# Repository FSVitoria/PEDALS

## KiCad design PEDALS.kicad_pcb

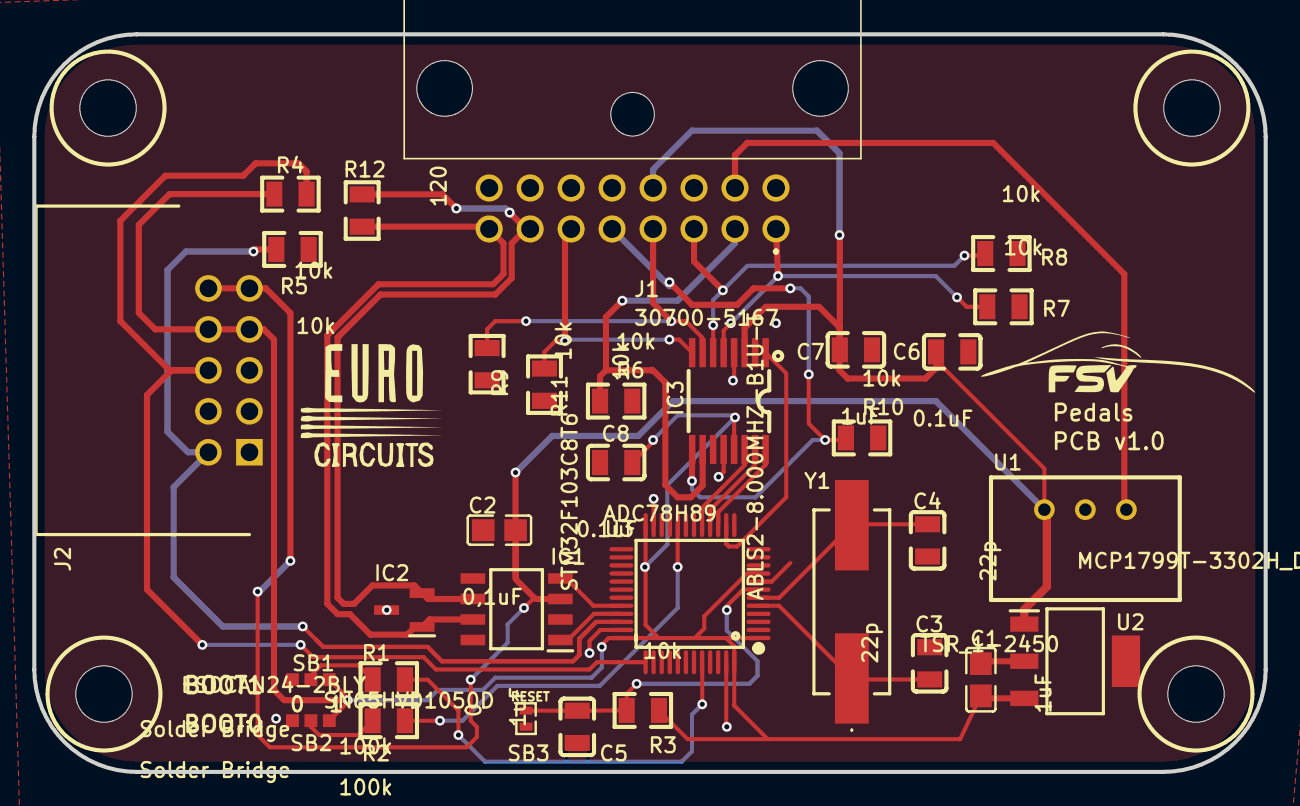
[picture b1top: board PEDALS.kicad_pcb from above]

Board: 2 copper layers, 76.3 x 45.7 mm, 36 parts (0 on the bottom side), 27 nets.

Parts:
C1, C5, C7: 1uF; C0805
C2: 0,1uF; C0805
C3, C4: 22p; C0805
C6, C8: 0.1uF; C0805
Hole_gge27180: Hole_gge27180
Hole_gge27183: Hole_gge27183
Hole_gge27186: Hole_gge27186
Hole_gge27189: Hole_gge27189
IC1: SN65HVD1050D; SOIC127P600X175-8N
IC2: ESDCAN24-2BLY; SOT105P255X150-3N
IC3: ADC78H89; TSSOP-16_L5.0-W4.4-P0.65-LS6.4-BL
J1: 30700-5167; 307005167
J2: 61201021721; SHDRRA10W64P254X254_2X5_2036X8
R1, R2: 100k; R0805
R3, R4, R5, R6, R7, R8, R9, R10, R11: 10k; R0805
R12: 120; R0805
SB1, SB2: Solder Bridge; SOLDER BRDIGE
SB3: 0; R0402
U1: TSR_1-2450; TSR-1-24120
U2: MCP1799T-3302H_DB; SOT230P700X180-4N
U3: STM32F103C8T6; LQFP-48_L7.0-W7.0-P0.50-LS9.0-BL
Y1: ABLS2-8.000MHZ-B1U-T; ABLS

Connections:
3V3: C1.2, C8.1, IC3.13, J2.7, J2.8, R3.2, R4.2, SB1.1, SB2.1, U2.3, U3.1, U3.9, U3.24, U3.36, U3.48
+5V: C2.1, C6.2, C7.2, IC1.3, IC3.3, J1.12, J2.9, J2.10, U1.3, U2.1
+24V: J1.10, U1.1
BOOT0: R1.1, U3.44
BOOT1: R2.1, U3.20
CAN_H: IC1.7, IC2.1, J1.8, R12.2
CAN_L: IC1.6, IC2.2, J1.7, R12.1
CAN_RX: IC1.4, U3.32
CAN_TX: IC1.1, U3.33
GND: C1.1, C2.2, C3.2, C4.2, C5.1, C6.1, C7.1, C8.2, IC1.2, IC1.8, IC2.3, IC3.4, IC3.12, J1.13, J1.15, J1.16, J2.3, J2.4, R5.1, R6.2, R7.2, R8.2, R9.2, R10.2, R11.2, SB1.3, SB2.3, SB3.1, U1.2, U2.2, U2.4, U3.8, U3.23, U3.35, U3.47
R1_2: R1.2, SB1.2
R2_2: R2.2, SB2.2
RST: C5.2, R3.1, SB3.2, U3.7
SPI_CS1: IC3.1, U3.14
SPI_MISO: IC3.15, U3.16
SPI_MOSI: IC3.14, U3.17
SPI_SCK: IC3.16, U3.15
SWCLK: J2.6, R4.1, U3.37
SWDIO: J2.2, R5.2, U3.34
VA_1: IC3.6, J1.3, R8.1
VA_2: IC3.5, J1.1, R7.1
VD_1: IC3.8, J1.6, R11.1
VD_2: IC3.7, J1.4, R9.1
VF_1: IC3.9, J1.5, R10.1
VF_2: IC3.10, J1.2, R6.1
Y1_1: C3.1, U3.5, Y1.1
Y1_2: C4.1, U3.6, Y1.2
